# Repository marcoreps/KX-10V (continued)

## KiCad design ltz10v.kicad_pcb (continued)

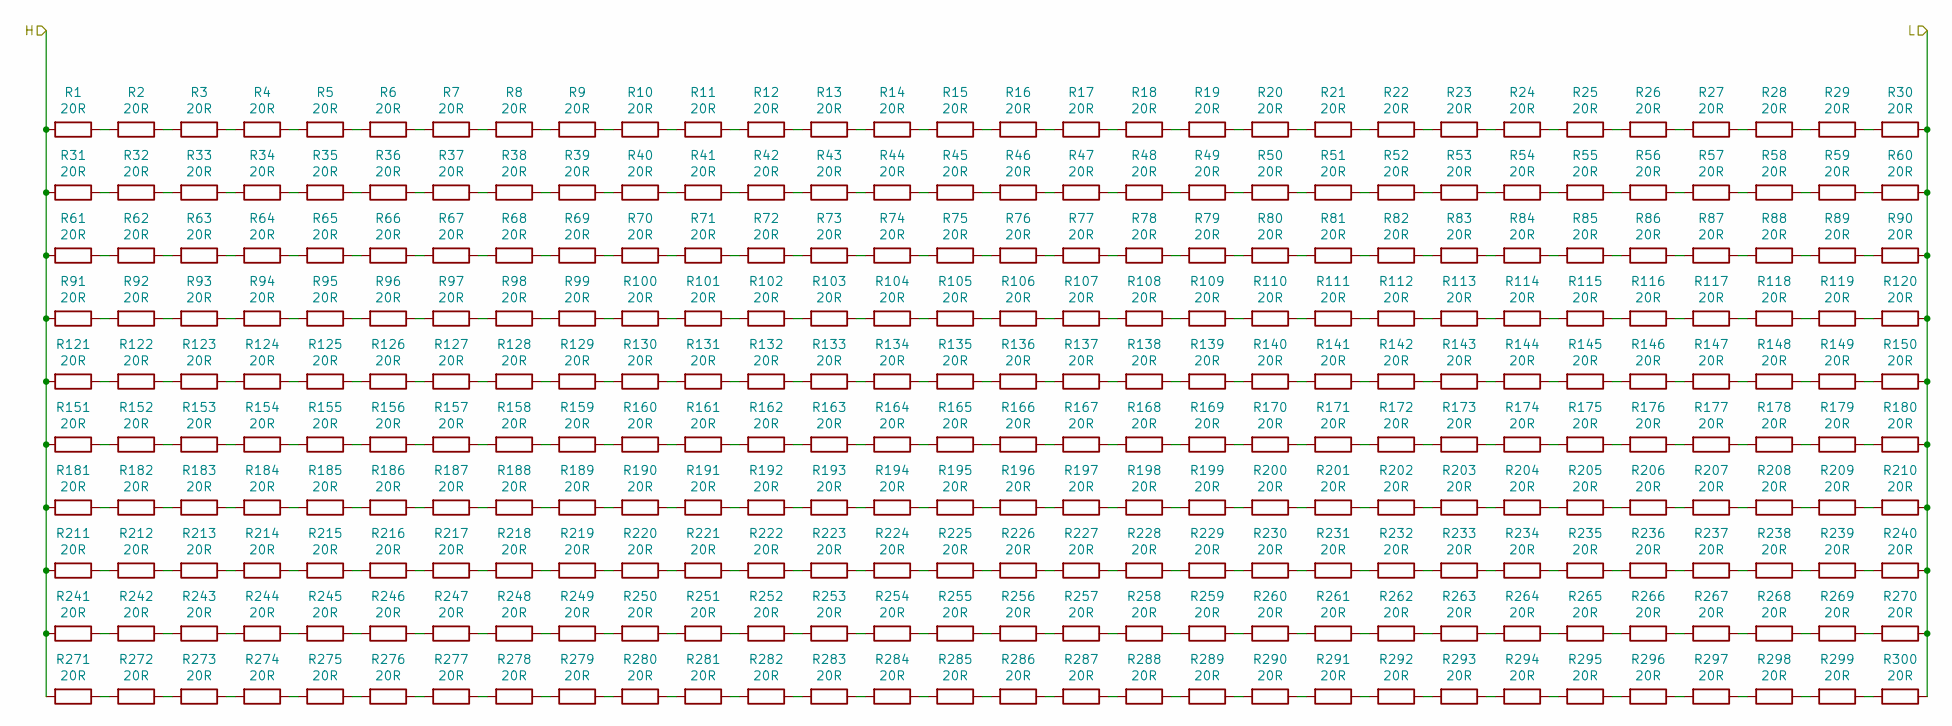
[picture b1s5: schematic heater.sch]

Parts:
R301, R302, R303, R304, R305, R306, R307, R308, R309, R310, R311, R312, R313, R314, R315, R316, R317, R318, R319, R320, R321, R322, R323, R324, R325, R326, R327, R328, R329, R330, R331, R332, R333, R334, R335, R336, R337, R338, R339, R340, R341, R342, R343, R344, R345, R346, R347, R348, R349, R350, R351, R352, R353, R354, R355, R356, R357, R358, R359, R360, R361, R362, R363, R364, R365, R366, R367, R368, R369, R370, R371, R372, R373, R374, R375, R376, R377, R378, R379, R380, R381, R382, R383, R384, R385, R386, R387, R388, R389, R390, R391, R392, R393, R394, R395, R396, R397, R398, R399, R400, R401, R402, R403, R404, R405, R406, R407, R408, R409, R410, R411, R412, R413, R414, R415, R416, R417, R418, R419, R420, R421, R422, R423, R424, R425, R426, R427, R428, R429, R430, R431, R432, R433, R434, R435, R436, R437, R438, R439, R440, R441, R442, R443, R444, R445, R446, R447, R448, R449, R450, R451, R452, R453, R454, R455, R456, R457, R458, R459, R460, R461, R462, R463, R464, R465, R466, R467, R468, R469, R470, R471, R472, R473, R474, R475, R476, R477, R478, R479, R480, R481, R482, R483, R484, R485, R486, R487, R488, R489, R490, R491, R492, R493, R494, R495, R496, R497, R498, R499, R500, R501, R502, R503, R504, R505, R506, R507, R508, R509, R510, R511, R512, R513, R514, R515, R516, R517, R518, R519, R520, R521, R522, R523, R524, R525, R526, R527, R528, R529, R530, R531, R532, R533, R534, R535, R536, R537, R538, R539, R540, R541, R542, R543, R544, R545, R546, R547, R548, R549, R550, R551, R552, R553, R554, R555, R556, R557, R558, R559, R560, R561, R562, R563, R564, R565, R566, R567, R568, R569, R570, R571, R572, R573, R574, R575, R576, R577, R578, R579, R580, R581, R582, R583, R584, R585, R586, R587, R588, R589, R590, R591, R592, R593, R594, R595, R596, R597, R598, R599, R600: 20R; R_0402_1005Metric; LCSC C25089

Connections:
/temperature/sheet5FAD990D/H: R301.2, R331.2, R361.2, R391.2, R421.2, R451.2, R481.2, R511.2, R541.2, R571.2; also elsewhere on the board
GND: R330.1, R360.1, R390.1, R420.1, R450.1, R480.1, R510.1, R540.1, R570.1, R600.1; also elsewhere on the board
unnamed: R301.1, R302.2
unnamed: R302.1, R303.2
unnamed: R303.1, R304.2
unnamed: R304.1, R305.2
unnamed: R305.1, R306.2
unnamed: R306.1, R307.2
unnamed: R307.1, R308.2
unnamed: R308.1, R309.2
unnamed: R309.1, R310.2
unnamed: R310.1, R311.2
unnamed: R311.1, R312.2
unnamed: R312.1, R313.2
unnamed: R313.1, R314.2
unnamed: R314.1, R315.2
unnamed: R315.1, R316.2
unnamed: R316.1, R317.2
unnamed: R317.1, R318.2
unnamed: R318.1, R319.2
unnamed: R319.1, R320.2
unnamed: R320.1, R321.2
unnamed: R321.1, R322.2
unnamed: R322.1, R323.2
unnamed: R323.1, R324.2
unnamed: R324.1, R325.2
unnamed: R325.1, R326.2
unnamed: R326.1, R327.2
unnamed: R327.1, R328.2
unnamed: R328.1, R329.2
unnamed: R329.1, R330.2
unnamed: R331.1, R332.2
unnamed: R332.1, R333.2
unnamed: R333.1, R334.2
unnamed: R334.1, R335.2
unnamed: R335.1, R336.2
unnamed: R336.1, R337.2
unnamed: R337.1, R338.2
unnamed: R338.1, R339.2
unnamed: R339.1, R340.2
unnamed: R340.1, R341.2
unnamed: R341.1, R342.2
unnamed: R342.1, R343.2
unnamed: R343.1, R344.2
unnamed: R344.1, R345.2
unnamed: R345.1, R346.2
unnamed: R346.1, R347.2
unnamed: R347.1, R348.2
unnamed: R348.1, R349.2
unnamed: R349.1, R350.2
unnamed: R350.1, R351.2
unnamed: R351.1, R352.2
unnamed: R352.1, R353.2
unnamed: R353.1, R354.2
unnamed: R354.1, R355.2
unnamed: R355.1, R356.2
unnamed: R356.1, R357.2
unnamed: R357.1, R358.2
unnamed: R358.1, R359.2
unnamed: R359.1, R360.2
unnamed: R361.1, R362.2
unnamed: R362.1, R363.2
unnamed: R363.1, R364.2
unnamed: R364.1, R365.2
unnamed: R365.1, R366.2
unnamed: R366.1, R367.2
unnamed: R367.1, R368.2
unnamed: R368.1, R369.2
unnamed: R369.1, R370.2
unnamed: R370.1, R371.2
unnamed: R371.1, R372.2
unnamed: R372.1, R373.2
unnamed: R373.1, R374.2
unnamed: R374.1, R375.2
unnamed: R375.1, R376.2
unnamed: R376.1, R377.2
unnamed: R377.1, R378.2
unnamed: R378.1, R379.2
unnamed: R379.1, R380.2
unnamed: R380.1, R381.2
unnamed: R381.1, R382.2
unnamed: R382.1, R383.2
unnamed: R383.1, R384.2
unnamed: R384.1, R385.2
unnamed: R385.1, R386.2
unnamed: R386.1, R387.2
unnamed: R387.1, R388.2
unnamed: R388.1, R389.2
unnamed: R389.1, R390.2
unnamed: R391.1, R392.2
unnamed: R392.1, R393.2
unnamed: R393.1, R394.2
unnamed: R394.1, R395.2
unnamed: R395.1, R396.2
unnamed: R396.1, R397.2
unnamed: R397.1, R398.2
unnamed: R398.1, R399.2
unnamed: R399.1, R400.2
unnamed: R400.1, R401.2
unnamed: R401.1, R402.2
unnamed: R402.1, R403.2
unnamed: R403.1, R404.2
unnamed: R404.1, R405.2
unnamed: R405.1, R406.2
unnamed: R406.1, R407.2
unnamed: R407.1, R408.2
unnamed: R408.1, R409.2
unnamed: R409.1, R410.2
unnamed: R410.1, R411.2
unnamed: R411.1, R412.2
unnamed: R412.1, R413.2
unnamed: R413.1, R414.2
unnamed: R414.1, R415.2
unnamed: R415.1, R416.2
unnamed: R416.1, R417.2
unnamed: R417.1, R418.2
unnamed: R418.1, R419.2
unnamed: R419.1, R420.2
unnamed: R421.1, R422.2
unnamed: R422.1, R423.2
unnamed: R423.1, R424.2
unnamed: R424.1, R425.2
unnamed: R425.1, R426.2
unnamed: R426.1, R427.2
unnamed: R427.1, R428.2
unnamed: R428.1, R429.2
unnamed: R429.1, R430.2
unnamed: R430.1, R431.2
unnamed: R431.1, R432.2
unnamed: R432.1, R433.2
unnamed: R433.1, R434.2
unnamed: R434.1, R435.2
unnamed: R435.1, R436.2
unnamed: R436.1, R437.2
unnamed: R437.1, R438.2
unnamed: R438.1, R439.2
unnamed: R439.1, R440.2
unnamed: R440.1, R441.2
unnamed: R441.1, R442.2
unnamed: R442.1, R443.2
unnamed: R443.1, R444.2
unnamed: R444.1, R445.2
unnamed: R445.1, R446.2
unnamed: R446.1, R447.2
unnamed: R447.1, R448.2
unnamed: R448.1, R449.2
unnamed: R449.1, R450.2
unnamed: R451.1, R452.2
unnamed: R452.1, R453.2
unnamed: R453.1, R454.2
unnamed: R454.1, R455.2
unnamed: R455.1, R456.2
unnamed: R456.1, R457.2
unnamed: R457.1, R458.2
unnamed: R458.1, R459.2
unnamed: R459.1, R460.2
unnamed: R460.1, R461.2
unnamed: R461.1, R462.2
unnamed: R462.1, R463.2
unnamed: R463.1, R464.2
unnamed: R464.1, R465.2
unnamed: R465.1, R466.2
unnamed: R466.1, R467.2
unnamed: R467.1, R468.2
unnamed: R468.1, R469.2
unnamed: R469.1, R470.2
unnamed: R470.1, R471.2
unnamed: R471.1, R472.2
unnamed: R472.1, R473.2
unnamed: R473.1, R474.2
unnamed: R474.1, R475.2
unnamed: R475.1, R476.2
unnamed: R476.1, R477.2
unnamed: R477.1, R478.2
unnamed: R478.1, R479.2
unnamed: R479.1, R480.2
unnamed: R481.1, R482.2
unnamed: R482.1, R483.2
unnamed: R483.1, R484.2
unnamed: R484.1, R485.2
unnamed: R485.1, R486.2
unnamed: R486.1, R487.2
unnamed: R487.1, R488.2
unnamed: R488.1, R489.2
unnamed: R489.1, R490.2
unnamed: R490.1, R491.2
unnamed: R491.1, R492.2
unnamed: R492.1, R493.2
unnamed: R493.1, R494.2
unnamed: R494.1, R495.2
unnamed: R495.1, R496.2
unnamed: R496.1, R497.2
unnamed: R497.1, R498.2
unnamed: R498.1, R499.2
unnamed: R499.1, R500.2
unnamed: R500.1, R501.2
unnamed: R501.1, R502.2
unnamed: R502.1, R503.2
unnamed: R503.1, R504.2
unnamed: R504.1, R505.2
unnamed: R505.1, R506.2
unnamed: R506.1, R507.2
unnamed: R507.1, R508.2
unnamed: R508.1, R509.2
unnamed: R509.1, R510.2
unnamed: R511.1, R512.2
unnamed: R512.1, R513.2
unnamed: R513.1, R514.2
unnamed: R514.1, R515.2
unnamed: R515.1, R516.2
unnamed: R516.1, R517.2
unnamed: R517.1, R518.2
unnamed: R518.1, R519.2
unnamed: R519.1, R520.2
unnamed: R520.1, R521.2
unnamed: R521.1, R522.2
unnamed: R522.1, R523.2
unnamed: R523.1, R524.2
unnamed: R524.1, R525.2
unnamed: R525.1, R526.2
unnamed: R526.1, R527.2
unnamed: R527.1, R528.2
unnamed: R528.1, R529.2
unnamed: R529.1, R530.2
unnamed: R530.1, R531.2
unnamed: R531.1, R532.2
unnamed: R532.1, R533.2
unnamed: R533.1, R534.2
unnamed: R534.1, R535.2
unnamed: R535.1, R536.2
unnamed: R536.1, R537.2
unnamed: R537.1, R538.2
unnamed: R538.1, R539.2
unnamed: R539.1, R540.2
unnamed: R541.1, R542.2
unnamed: R542.1, R543.2
unnamed: R543.1, R544.2
unnamed: R544.1, R545.2
unnamed: R545.1, R546.2
unnamed: R546.1, R547.2
unnamed: R547.1, R548.2
unnamed: R548.1, R549.2
unnamed: R549.1, R550.2
unnamed: R550.1, R551.2
unnamed: R551.1, R552.2
unnamed: R552.1, R553.2
unnamed: R553.1, R554.2
unnamed: R554.1, R555.2
unnamed: R555.1, R556.2
unnamed: R556.1, R557.2
unnamed: R557.1, R558.2
unnamed: R558.1, R559.2
unnamed: R559.1, R560.2
unnamed: R560.1, R561.2
unnamed: R561.1, R562.2
unnamed: R562.1, R563.2
unnamed: R563.1, R564.2
unnamed: R564.1, R565.2
unnamed: R565.1, R566.2
unnamed: R566.1, R567.2
unnamed: R567.1, R568.2
unnamed: R568.1, R569.2
unnamed: R569.1, R570.2
unnamed: R571.1, R572.2
unnamed: R572.1, R573.2
unnamed: R573.1, R574.2
unnamed: R574.1, R575.2
unnamed: R575.1, R576.2
unnamed: R576.1, R577.2
unnamed: R577.1, R578.2
unnamed: R578.1, R579.2
unnamed: R579.1, R580.2
unnamed: R580.1, R581.2
unnamed: R581.1, R582.2
unnamed: R582.1, R583.2
unnamed: R583.1, R584.2
unnamed: R584.1, R585.2
unnamed: R585.1, R586.2
unnamed: R586.1, R587.2
unnamed: R587.1, R588.2
unnamed: R588.1, R589.2
unnamed: R589.1, R590.2
unnamed: R590.1, R591.2
unnamed: R591.1, R592.2
unnamed: R592.1, R593.2
unnamed: R593.1, R594.2
unnamed: R594.1, R595.2
unnamed: R595.1, R596.2
unnamed: R596.1, R597.2
unnamed: R597.1, R598.2
unnamed: R598.1, R599.2
unnamed: R599.1, R600.2

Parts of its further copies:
R1, R2, R3, R4, R5, R6, R7, R8, R9, R10, R11, R12, R13, R14, R15, R16, R17, R18, R19, R20, R21, R22, R23, R24, R25, R26, R27, R28, R29, R30, R31, R32, R33, R34, R35, R36, R37, R38, R39, R40, R41, R42, R43, R44, R45, R46, R47, R48, R49, R50, R51, R52, R53, R54, R55, R56, R57, R58, R59, R60, R61, R62, R63, R64, R65, R66, R67, R68, R69, R70, R71, R72, R73, R74, R75, R76, R77, R78, R79, R80, R81, R82, R83, R84, R85, R86, R87, R88, R89, R90, R91, R92, R93, R94, R95, R96, R97, R98, R99, R100, R101, R102, R103, R104, R105, R106, R107, R108, R109, R110, R111, R112, R113, R114, R115, R116, R117, R118, R119, R120, R121, R122, R123, R124, R125, R126, R127, R128, R129, R130, R131, R132, R133, R134, R135, R136, R137, R138, R139, R140, R141, R142, R143, R144, R145, R146, R147, R148, R149, R150, R151, R152, R153, R154, R155, R156, R157, R158, R159, R160, R161, R162, R163, R164, R165, R166, R167, R168, R169, R170, R171, R172, R173, R174, R175, R176, R177, R178, R179, R180, R181, R182, R183, R184, R185, R186, R187, R188, R189, R190, R191, R192, R193, R194, R195, R196, R197, R198, R199, R200, R201, R202, R203, R204, R205, R206, R207, R208, R209, R210, R211, R212, R213, R214, R215, R216, R217, R218, R219, R220, R221, R222, R223, R224, R225, R226, R227, R228, R229, R230, R231, R232, R233, R234, R235, R236, R237, R238, R239, R240, R241, R242, R243, R244, R245, R246, R247, R248, R249, R250, R251, R252, R253, R254, R255, R256, R257, R258, R259, R260, R261, R262, R263, R264, R265, R266, R267, R268, R269, R270, R271, R272, R273, R274, R275, R276, R277, R278, R279, R280, R281, R282, R283, R284, R285, R286, R287, R288, R289, R290, R291, R292, R293, R294, R295, R296, R297, R298, R299, R300, R601, R602, R603, R604, R605, R606, R607, R608, R609, R610, R611, R612, R613, R614, R615, R616, R617, R618, R619, R620, R621, R622, R623, R624, R625, R626, R627, R628, R629, R630, R631, R632, R633, R634, R635, R636, R637, R638, R639, R640, R641, R642, R643, R644, R645, R646, R647, R648, R649, R650, R651, R652, R653, R654, R655, R656, R657, R658, R659, R660, R661, R662, R663, R664, R665, R666, R667, R668, R669, R670, R671, R672, R673, R674, R675, R676, R677, R678, R679, R680, R681, R682, R683, R684, R685, R686, R687, R688, R689, R690, R691, R692, R693, R694, R695, R696, R697, R698, R699, R700, R701, R702, R703, R704, R705, R706, R707, R708, R709, R710, R711, R712, R713, R714, R715, R716, R717, R718, R719, R720, R721, R722, R723, R724, R725, R726, R727, R728, R729, R730, R731, R732, R733, R734, R735, R736, R737, R738, R739, R740, R741, R742, R743, R744, R745, R746, R747, R748, R749, R750, R751, R752, R753, R754, R755, R756, R757, R758, R759, R760, R761, R762, R763, R764, R765, R766, R767, R768, R769, R770, R771, R772, R773, R774, R775, R776, R777, R778, R779, R780, R781, R782, R783, R784, R785, R786, R787, R788, R789, R790, R791, R792, R793, R794, R795, R796, R797, R798, R799, R800, R801, R802, R803, R804, R805, R806, R807, R808, R809, R810, R811, R812, R813, R814, R815, R816, R817, R818, R819, R820, R821, R822, R823, R824, R825, R826, R827, R828, R829, R830, R831, R832, R833, R834, R835, R836, R837, R838, R839, R840, R841, R842, R843, R844, R845, R846, R847, R848, R849, R850, R851, R852, R853, R854, R855, R856, R857, R858, R859, R860, R861, R862, R863, R864, R865, R866, R867, R868, R869, R870, R871, R872, R873, R874, R875, R876, R877, R878, R879, R880, R881, R882, R883, R884, R885, R886, R887, R888, R889, R890, R891, R892, R893, R894, R895, R896, R897, R898, R899, R900: 20R; R_0402_1005Metric; LCSC C25089

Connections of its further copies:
/temperature/sheet5FAD990D/H: R1.2, R31.2, R61.2, R91.2, R121.2, R151.2, R181.2, R211.2, R241.2, R271.2, R601.2, R631.2, R661.2, R691.2, R721.2, R751.2, R781.2, R811.2, R841.2, R871.2; also elsewhere on the board
GND: R30.1, R60.1, R90.1, R120.1, R150.1, R180.1, R210.1, R240.1, R270.1, R300.1, R630.1, R660.1, R690.1, R720.1, R750.1, R780.1, R810.1, R840.1, R870.1, R900.1; also elsewhere on the board
unnamed: R1.1, R2.2
unnamed: R2.1, R3.2
unnamed: R3.1, R4.2
unnamed: R4.1, R5.2
unnamed: R5.1, R6.2
unnamed: R6.1, R7.2
unnamed: R7.1, R8.2
unnamed: R8.1, R9.2
unnamed: R10.1, R11.2
unnamed: R9.1, R10.2
unnamed: R11.1, R12.2
unnamed: R12.1, R13.2
unnamed: R13.1, R14.2
unnamed: R14.1, R15.2
unnamed: R15.1, R16.2
unnamed: R16.1, R17.2
unnamed: R17.1, R18.2
unnamed: R18.1, R19.2
unnamed: R19.1, R20.2
unnamed: R20.1, R21.2
unnamed: R21.1, R22.2
unnamed: R22.1, R23.2
unnamed: R23.1, R24.2
unnamed: R24.1, R25.2
unnamed: R25.1, R26.2
unnamed: R26.1, R27.2
unnamed: R27.1, R28.2
unnamed: R28.1, R29.2
unnamed: R29.1, R30.2
unnamed: R31.1, R32.2
unnamed: R32.1, R33.2
unnamed: R33.1, R34.2
unnamed: R34.1, R35.2
unnamed: R35.1, R36.2
unnamed: R36.1, R37.2
unnamed: R37.1, R38.2
unnamed: R38.1, R39.2
unnamed: R39.1, R40.2
unnamed: R40.1, R41.2
unnamed: R41.1, R42.2
unnamed: R42.1, R43.2
unnamed: R43.1, R44.2
unnamed: R44.1, R45.2
unnamed: R45.1, R46.2
unnamed: R46.1, R47.2
unnamed: R47.1, R48.2
unnamed: R48.1, R49.2
unnamed: R49.1, R50.2
unnamed: R50.1, R51.2
unnamed: R51.1, R52.2
unnamed: R52.1, R53.2
unnamed: R53.1, R54.2
unnamed: R54.1, R55.2
unnamed: R55.1, R56.2
unnamed: R56.1, R57.2
unnamed: R57.1, R58.2
unnamed: R58.1, R59.2
unnamed: R59.1, R60.2
unnamed: R61.1, R62.2
unnamed: R62.1, R63.2
unnamed: R63.1, R64.2
unnamed: R64.1, R65.2
unnamed: R65.1, R66.2
unnamed: R66.1, R67.2
unnamed: R67.1, R68.2
unnamed: R68.1, R69.2
unnamed: R69.1, R70.2
unnamed: R70.1, R71.2
unnamed: R71.1, R72.2
unnamed: R72.1, R73.2
unnamed: R73.1, R74.2
unnamed: R74.1, R75.2
unnamed: R75.1, R76.2
unnamed: R76.1, R77.2
unnamed: R77.1, R78.2
unnamed: R78.1, R79.2
unnamed: R79.1, R80.2
unnamed: R80.1, R81.2
unnamed: R81.1, R82.2
unnamed: R82.1, R83.2
unnamed: R83.1, R84.2
unnamed: R84.1, R85.2
unnamed: R85.1, R86.2
unnamed: R86.1, R87.2
unnamed: R87.1, R88.2
unnamed: R88.1, R89.2
unnamed: R89.1, R90.2
unnamed: R91.1, R92.2
unnamed: R92.1, R93.2
unnamed: R93.1, R94.2
unnamed: R94.1, R95.2
unnamed: R95.1, R96.2
unnamed: R96.1, R97.2
unnamed: R97.1, R98.2
unnamed: R98.1, R99.2
unnamed: R100.1, R101.2
unnamed: R99.1, R100.2
unnamed: R101.1, R102.2
unnamed: R102.1, R103.2
unnamed: R103.1, R104.2
unnamed: R104.1, R105.2
unnamed: R105.1, R106.2
unnamed: R106.1, R107.2
unnamed: R107.1, R108.2
unnamed: R108.1, R109.2
unnamed: R109.1, R110.2
unnamed: R110.1, R111.2
unnamed: R111.1, R112.2
unnamed: R112.1, R113.2
unnamed: R113.1, R114.2
unnamed: R114.1, R115.2
unnamed: R115.1, R116.2
unnamed: R116.1, R117.2
unnamed: R117.1, R118.2
unnamed: R118.1, R119.2
unnamed: R119.1, R120.2
unnamed: R121.1, R122.2
unnamed: R122.1, R123.2
unnamed: R123.1, R124.2
unnamed: R124.1, R125.2
unnamed: R125.1, R126.2
unnamed: R126.1, R127.2
unnamed: R127.1, R128.2
unnamed: R128.1, R129.2
unnamed: R129.1, R130.2
unnamed: R130.1, R131.2
unnamed: R131.1, R132.2
unnamed: R132.1, R133.2
unnamed: R133.1, R134.2
unnamed: R134.1, R135.2
unnamed: R135.1, R136.2
unnamed: R136.1, R137.2
unnamed: R137.1, R138.2
unnamed: R138.1, R139.2
unnamed: R139.1, R140.2
unnamed: R140.1, R141.2
unnamed: R141.1, R142.2
unnamed: R142.1, R143.2
unnamed: R143.1, R144.2
unnamed: R144.1, R145.2
unnamed: R145.1, R146.2
unnamed: R146.1, R147.2
unnamed: R147.1, R148.2
unnamed: R148.1, R149.2
unnamed: R149.1, R150.2
unnamed: R151.1, R152.2
unnamed: R152.1, R153.2
unnamed: R153.1, R154.2
unnamed: R154.1, R155.2
unnamed: R155.1, R156.2
unnamed: R156.1, R157.2
unnamed: R157.1, R158.2
unnamed: R158.1, R159.2
unnamed: R159.1, R160.2
unnamed: R160.1, R161.2
unnamed: R161.1, R162.2
unnamed: R162.1, R163.2
unnamed: R163.1, R164.2
unnamed: R164.1, R165.2
unnamed: R165.1, R166.2
unnamed: R166.1, R167.2
unnamed: R167.1, R168.2
unnamed: R168.1, R169.2
unnamed: R169.1, R170.2
unnamed: R170.1, R171.2
unnamed: R171.1, R172.2
unnamed: R172.1, R173.2
unnamed: R173.1, R174.2
unnamed: R174.1, R175.2
unnamed: R175.1, R176.2
unnamed: R176.1, R177.2
unnamed: R177.1, R178.2
unnamed: R178.1, R179.2
unnamed: R179.1, R180.2
unnamed: R181.1, R182.2
unnamed: R182.1, R183.2
unnamed: R183.1, R184.2
unnamed: R184.1, R185.2
unnamed: R185.1, R186.2
unnamed: R186.1, R187.2
unnamed: R187.1, R188.2
unnamed: R188.1, R189.2
unnamed: R189.1, R190.2
unnamed: R190.1, R191.2
unnamed: R191.1, R192.2
unnamed: R192.1, R193.2
unnamed: R193.1, R194.2
unnamed: R194.1, R195.2
unnamed: R195.1, R196.2
unnamed: R196.1, R197.2
unnamed: R197.1, R198.2
unnamed: R198.1, R199.2
unnamed: R199.1, R200.2
unnamed: R200.1, R201.2
unnamed: R201.1, R202.2
unnamed: R202.1, R203.2
unnamed: R203.1, R204.2
unnamed: R204.1, R205.2
unnamed: R205.1, R206.2
unnamed: R206.1, R207.2
unnamed: R207.1, R208.2
unnamed: R208.1, R209.2
unnamed: R209.1, R210.2
unnamed: R211.1, R212.2
unnamed: R212.1, R213.2
unnamed: R213.1, R214.2
unnamed: R214.1, R215.2
unnamed: R215.1, R216.2
unnamed: R216.1, R217.2
unnamed: R217.1, R218.2
unnamed: R218.1, R219.2
unnamed: R219.1, R220.2
unnamed: R220.1, R221.2
unnamed: R221.1, R222.2
unnamed: R222.1, R223.2
unnamed: R223.1, R224.2
unnamed: R224.1, R225.2
unnamed: R225.1, R226.2
unnamed: R226.1, R227.2
unnamed: R227.1, R228.2
unnamed: R228.1, R229.2
unnamed: R229.1, R230.2
unnamed: R230.1, R231.2
unnamed: R231.1, R232.2
unnamed: R232.1, R233.2
unnamed: R233.1, R234.2
unnamed: R234.1, R235.2
unnamed: R235.1, R236.2
unnamed: R236.1, R237.2
unnamed: R237.1, R238.2
unnamed: R238.1, R239.2
unnamed: R239.1, R240.2
unnamed: R241.1, R242.2
unnamed: R242.1, R243.2
unnamed: R243.1, R244.2
unnamed: R244.1, R245.2
unnamed: R245.1, R246.2
unnamed: R246.1, R247.2
unnamed: R247.1, R248.2
unnamed: R248.1, R249.2
unnamed: R249.1, R250.2
unnamed: R250.1, R251.2
unnamed: R251.1, R252.2
unnamed: R252.1, R253.2
unnamed: R253.1, R254.2
unnamed: R254.1, R255.2
unnamed: R255.1, R256.2
unnamed: R256.1, R257.2
unnamed: R257.1, R258.2
unnamed: R258.1, R259.2
unnamed: R259.1, R260.2
unnamed: R260.1, R261.2
unnamed: R261.1, R262.2
unnamed: R262.1, R263.2
unnamed: R263.1, R264.2
unnamed: R264.1, R265.2
unnamed: R265.1, R266.2
unnamed: R266.1, R267.2
unnamed: R267.1, R268.2
unnamed: R268.1, R269.2
unnamed: R269.1, R270.2
unnamed: R271.1, R272.2
unnamed: R272.1, R273.2
unnamed: R273.1, R274.2
unnamed: R274.1, R275.2
unnamed: R275.1, R276.2
unnamed: R276.1, R277.2
unnamed: R277.1, R278.2
unnamed: R278.1, R279.2
unnamed: R279.1, R280.2
unnamed: R280.1, R281.2
unnamed: R281.1, R282.2
unnamed: R282.1, R283.2
unnamed: R283.1, R284.2
unnamed: R284.1, R285.2
unnamed: R285.1, R286.2
unnamed: R286.1, R287.2
unnamed: R287.1, R288.2
unnamed: R288.1, R289.2
unnamed: R289.1, R290.2
unnamed: R290.1, R291.2
unnamed: R291.1, R292.2
unnamed: R292.1, R293.2
unnamed: R293.1, R294.2
unnamed: R294.1, R295.2
unnamed: R295.1, R296.2
unnamed: R296.1, R297.2
unnamed: R297.1, R298.2
unnamed: R298.1, R299.2
unnamed: R299.1, R300.2
unnamed: R601.1, R602.2
unnamed: R602.1, R603.2
unnamed: R603.1, R604.2
unnamed: R604.1, R605.2
unnamed: R605.1, R606.2
unnamed: R606.1, R607.2
unnamed: R607.1, R608.2
unnamed: R608.1, R609.2
unnamed: R609.1, R610.2
unnamed: R610.1, R611.2
unnamed: R611.1, R612.2
unnamed: R612.1, R613.2
unnamed: R613.1, R614.2
unnamed: R614.1, R615.2
unnamed: R615.1, R616.2
unnamed: R616.1, R617.2
unnamed: R617.1, R618.2
unnamed: R618.1, R619.2
unnamed: R619.1, R620.2
unnamed: R620.1, R621.2
unnamed: R621.1, R622.2
unnamed: R622.1, R623.2
unnamed: R623.1, R624.2
unnamed: R624.1, R625.2
unnamed: R625.1, R626.2
unnamed: R626.1, R627.2
unnamed: R627.1, R628.2
unnamed: R628.1, R629.2
unnamed: R629.1, R630.2
unnamed: R631.1, R632.2
unnamed: R632.1, R633.2
unnamed: R633.1, R634.2
unnamed: R634.1, R635.2
unnamed: R635.1, R636.2
unnamed: R636.1, R637.2
unnamed: R637.1, R638.2
unnamed: R638.1, R639.2
unnamed: R639.1, R640.2
unnamed: R640.1, R641.2
unnamed: R641.1, R642.2
unnamed: R642.1, R643.2
unnamed: R643.1, R644.2
unnamed: R644.1, R645.2
unnamed: R645.1, R646.2
unnamed: R646.1, R647.2
unnamed: R647.1, R648.2
unnamed: R648.1, R649.2
unnamed: R649.1, R650.2
unnamed: R650.1, R651.2
unnamed: R651.1, R652.2
unnamed: R652.1, R653.2
unnamed: R653.1, R654.2
unnamed: R654.1, R655.2
unnamed: R655.1, R656.2
unnamed: R656.1, R657.2
unnamed: R657.1, R658.2
unnamed: R658.1, R659.2
unnamed: R659.1, R660.2
unnamed: R661.1, R662.2
unnamed: R662.1, R663.2
unnamed: R663.1, R664.2
unnamed: R664.1, R665.2
unnamed: R665.1, R666.2
unnamed: R666.1, R667.2
unnamed: R667.1, R668.2
unnamed: R668.1, R669.2
unnamed: R669.1, R670.2
unnamed: R670.1, R671.2
unnamed: R671.1, R672.2
unnamed: R672.1, R673.2
unnamed: R673.1, R674.2
unnamed: R674.1, R675.2
unnamed: R675.1, R676.2
unnamed: R676.1, R677.2
unnamed: R677.1, R678.2
unnamed: R678.1, R679.2
unnamed: R679.1, R680.2
unnamed: R680.1, R681.2
unnamed: R681.1, R682.2
unnamed: R682.1, R683.2
unnamed: R683.1, R684.2
unnamed: R684.1, R685.2
unnamed: R685.1, R686.2
unnamed: R686.1, R687.2
unnamed: R687.1, R688.2
unnamed: R688.1, R689.2
unnamed: R689.1, R690.2
unnamed: R691.1, R692.2
unnamed: R692.1, R693.2
unnamed: R693.1, R694.2
unnamed: R694.1, R695.2
unnamed: R695.1, R696.2
unnamed: R696.1, R697.2
unnamed: R697.1, R698.2
unnamed: R698.1, R699.2
unnamed: R699.1, R700.2
unnamed: R700.1, R701.2
unnamed: R701.1, R702.2
unnamed: R702.1, R703.2
unnamed: R703.1, R704.2
unnamed: R704.1, R705.2
unnamed: R705.1, R706.2
unnamed: R706.1, R707.2
unnamed: R707.1, R708.2
unnamed: R708.1, R709.2
unnamed: R709.1, R710.2
unnamed: R710.1, R711.2
unnamed: R711.1, R712.2
unnamed: R712.1, R713.2
unnamed: R713.1, R714.2
unnamed: R714.1, R715.2
unnamed: R715.1, R716.2
unnamed: R716.1, R717.2
unnamed: R717.1, R718.2
unnamed: R718.1, R719.2
unnamed: R719.1, R720.2
unnamed: R721.1, R722.2
unnamed: R722.1, R723.2
unnamed: R723.1, R724.2
unnamed: R724.1, R725.2
unnamed: R725.1, R726.2
unnamed: R726.1, R727.2
unnamed: R727.1, R728.2
unnamed: R728.1, R729.2
unnamed: R729.1, R730.2
unnamed: R730.1, R731.2
unnamed: R731.1, R732.2
unnamed: R732.1, R733.2
unnamed: R733.1, R734.2
unnamed: R734.1, R735.2
unnamed: R735.1, R736.2
unnamed: R736.1, R737.2
unnamed: R737.1, R738.2
unnamed: R738.1, R739.2
unnamed: R739.1, R740.2
unnamed: R740.1, R741.2
unnamed: R741.1, R742.2
unnamed: R742.1, R743.2
unnamed: R743.1, R744.2
unnamed: R744.1, R745.2
unnamed: R745.1, R746.2
unnamed: R746.1, R747.2
unnamed: R747.1, R748.2
unnamed: R748.1, R749.2
unnamed: R749.1, R750.2
unnamed: R751.1, R752.2
unnamed: R752.1, R753.2
unnamed: R753.1, R754.2
unnamed: R754.1, R755.2
unnamed: R755.1, R756.2
unnamed: R756.1, R757.2
unnamed: R757.1, R758.2
unnamed: R758.1, R759.2
unnamed: R759.1, R760.2
unnamed: R760.1, R761.2
unnamed: R761.1, R762.2
unnamed: R762.1, R763.2
unnamed: R763.1, R764.2
unnamed: R764.1, R765.2
unnamed: R765.1, R766.2
unnamed: R766.1, R767.2
unnamed: R767.1, R768.2
unnamed: R768.1, R769.2
unnamed: R769.1, R770.2
unnamed: R770.1, R771.2
unnamed: R771.1, R772.2
unnamed: R772.1, R773.2
unnamed: R773.1, R774.2
unnamed: R774.1, R775.2
unnamed: R775.1, R776.2
unnamed: R776.1, R777.2
unnamed: R777.1, R778.2
unnamed: R778.1, R779.2
unnamed: R779.1, R780.2
unnamed: R781.1, R782.2
unnamed: R782.1, R783.2
unnamed: R783.1, R784.2
unnamed: R784.1, R785.2
unnamed: R785.1, R786.2
unnamed: R786.1, R787.2
unnamed: R787.1, R788.2
unnamed: R788.1, R789.2
unnamed: R789.1, R790.2
unnamed: R790.1, R791.2
unnamed: R791.1, R792.2
unnamed: R792.1, R793.2
unnamed: R793.1, R794.2
unnamed: R794.1, R795.2
unnamed: R795.1, R796.2
unnamed: R796.1, R797.2
unnamed: R797.1, R798.2
unnamed: R798.1, R799.2
unnamed: R799.1, R800.2
unnamed: R800.1, R801.2
unnamed: R801.1, R802.2
unnamed: R802.1, R803.2
unnamed: R803.1, R804.2
unnamed: R804.1, R805.2
unnamed: R805.1, R806.2
unnamed: R806.1, R807.2
unnamed: R807.1, R808.2
unnamed: R808.1, R809.2
unnamed: R809.1, R810.2
unnamed: R811.1, R812.2
unnamed: R812.1, R813.2
unnamed: R813.1, R814.2
unnamed: R814.1, R815.2
unnamed: R815.1, R816.2
unnamed: R816.1, R817.2
unnamed: R817.1, R818.2
unnamed: R818.1, R819.2
unnamed: R819.1, R820.2
unnamed: R820.1, R821.2
unnamed: R821.1, R822.2
unnamed: R822.1, R823.2
unnamed: R823.1, R824.2
unnamed: R824.1, R825.2
unnamed: R825.1, R826.2
unnamed: R826.1, R827.2
unnamed: R827.1, R828.2
unnamed: R828.1, R829.2
unnamed: R829.1, R830.2
unnamed: R830.1, R831.2
unnamed: R831.1, R832.2
unnamed: R832.1, R833.2
unnamed: R833.1, R834.2
unnamed: R834.1, R835.2
unnamed: R835.1, R836.2
unnamed: R836.1, R837.2
unnamed: R837.1, R838.2
unnamed: R838.1, R839.2
unnamed: R839.1, R840.2
unnamed: R841.1, R842.2
unnamed: R842.1, R843.2
unnamed: R843.1, R844.2
unnamed: R844.1, R845.2
unnamed: R845.1, R846.2
unnamed: R846.1, R847.2
unnamed: R847.1, R848.2
unnamed: R848.1, R849.2
unnamed: R849.1, R850.2
unnamed: R850.1, R851.2
unnamed: R851.1, R852.2
unnamed: R852.1, R853.2
unnamed: R853.1, R854.2
unnamed: R854.1, R855.2
unnamed: R855.1, R856.2
unnamed: R856.1, R857.2
unnamed: R857.1, R858.2
unnamed: R858.1, R859.2
unnamed: R859.1, R860.2
unnamed: R860.1, R861.2
unnamed: R861.1, R862.2
unnamed: R862.1, R863.2
unnamed: R863.1, R864.2
unnamed: R864.1, R865.2
unnamed: R865.1, R866.2
unnamed: R866.1, R867.2
unnamed: R867.1, R868.2
unnamed: R868.1, R869.2
unnamed: R869.1, R870.2
unnamed: R871.1, R872.2
unnamed: R872.1, R873.2
unnamed: R873.1, R874.2
unnamed: R874.1, R875.2
unnamed: R875.1, R876.2
unnamed: R876.1, R877.2
unnamed: R877.1, R878.2
unnamed: R878.1, R879.2
unnamed: R879.1, R880.2
unnamed: R880.1, R881.2
unnamed: R881.1, R882.2
unnamed: R882.1, R883.2
unnamed: R883.1, R884.2
unnamed: R884.1, R885.2
unnamed: R885.1, R886.2
unnamed: R886.1, R887.2
unnamed: R887.1, R888.2
unnamed: R888.1, R889.2
unnamed: R889.1, R890.2
unnamed: R890.1, R891.2
unnamed: R891.1, R892.2
unnamed: R892.1, R893.2
unnamed: R893.1, R894.2
unnamed: R894.1, R895.2
unnamed: R895.1, R896.2
unnamed: R896.1, R897.2
unnamed: R897.1, R898.2
unnamed: R898.1, R899.2
unnamed: R899.1, R900.2

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
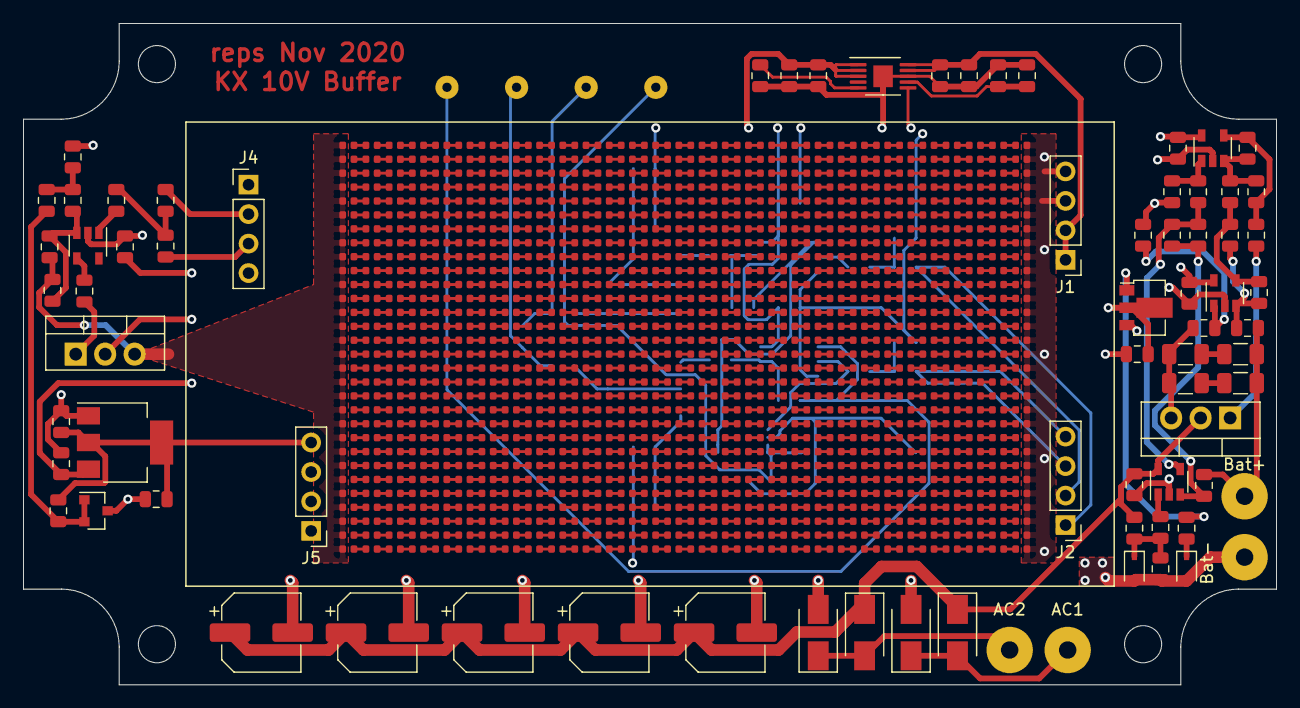
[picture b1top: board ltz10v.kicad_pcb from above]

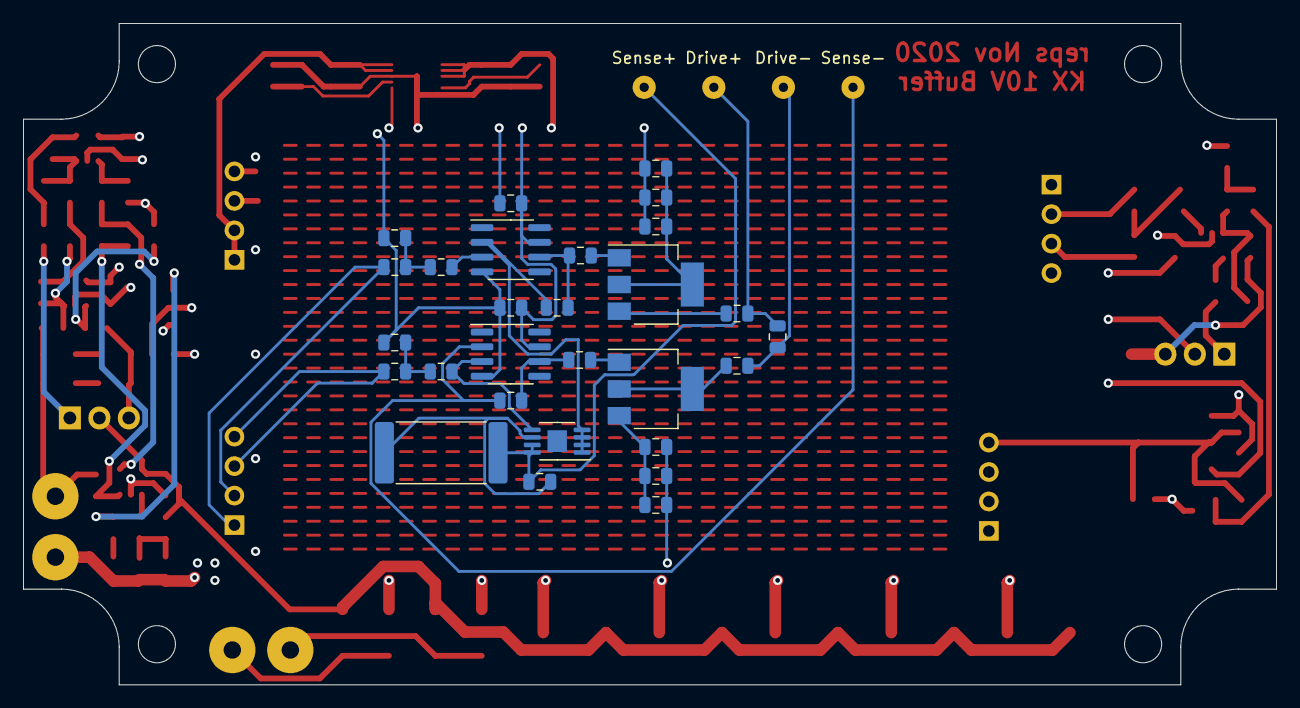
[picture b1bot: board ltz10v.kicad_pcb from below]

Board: 4 copper layers, 108.0 x 57.0 mm, 1012 parts (32 on the bottom side), 926 nets.

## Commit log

2020-11-02 srdgv
2020-11-02 added fab outputs
